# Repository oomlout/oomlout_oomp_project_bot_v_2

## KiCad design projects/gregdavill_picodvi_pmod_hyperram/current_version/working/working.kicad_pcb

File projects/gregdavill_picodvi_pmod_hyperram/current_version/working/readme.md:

# picodvi
 
## summary 
* id: gregdavill_picodvi_pmod_hyperram
* user: gregdavill
* name: picodvi
* board: pmod_hyperram
* repo: https://github.com/gregdavill/picodvi
* src_file_repo_kicad_pcb: hardware/pmod_hyperram/pmod_hyperram.kicad_pcb
* src_file_repo_kicad_pcb_link: https://github.com/gregdavill/picodvi/tree/master/hardware/pmod_hyperram/pmod_hyperram.kicad_pcb
* src_file_repo_kicad_sch: hardware/board/picodvi.kicad_sch
* src_file_repo_kicad_sch_link: https://github.com/gregdavill/picodvi/tree/master/hardware/board/picodvi.kicad_sch

* src_file_repo_sch: hardware/pmod_hyperram/pmod_hyperram.sch
* src_file_repo_sch_link: https://github.com/gregdavill/picodvi/tree/master/hardware/pmod_hyperram/pmod_hyperram.sch
* full details link: https://github.com/oomlout/oomlout_oomp_project_bot_v_2/tree/main/projects/gregdavill_picodvi_pmod_hyperram/current_version/working

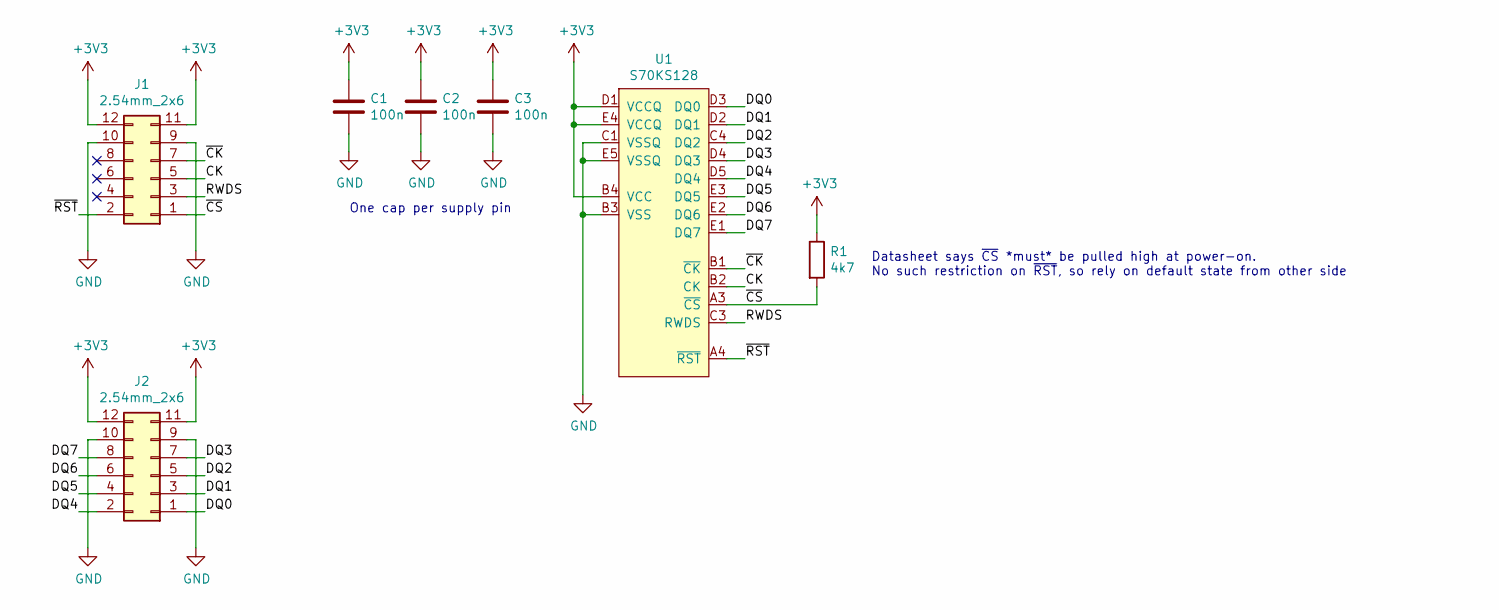
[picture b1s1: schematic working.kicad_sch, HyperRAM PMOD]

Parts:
C1, C2, C3: 100n; C_0402_1005Metric
J1, J2: 2.54mm_2x6; PinSocket_2x06_P2.54mm_Horizontal
R1: 4k7; R_0402_1005Metric
U1: S70KS128

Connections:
+3V3: C1.1, C2.1, C3.1, J1.11, J1.12, J2.11, J2.12, R1.1, U1.B4 (VCC), U1.D1 (VCCQ), U1.E4 (VCCQ)
/CK: J1.5, U1.B2 (CK)
/DQ0: J2.1, U1.D3 (DQ0)
/DQ1: J2.3, U1.D2 (DQ1)
/DQ2: J2.5, U1.C4 (DQ2)
/DQ3: J2.7, U1.D4 (DQ3)
/DQ4: J2.2, U1.D5 (DQ4)
/DQ5: J2.4, U1.E3 (DQ5)
/DQ6: J2.6, U1.E2 (DQ6)
/DQ7: J2.8, U1.E1 (DQ7)
/RWDS: J1.3, U1.C3 (RWDS)
/~CK: J1.7, U1.B1 (~CK)
/~CS: J1.1, R1.2, U1.A3 (~CS)
/~RST: J1.2, U1.A4 (~RST)
GND: C1.2, C2.2, C3.2, J1.9, J1.10, J2.9, J2.10, U1.B3 (VSS), U1.C1 (VSSQ), U1.E5 (VSSQ)

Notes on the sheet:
Datasheet says ~{CS} *must* be pulled high at power-on. No such restriction on ~{RST}, so rely on default state from other side
One cap per supply pin

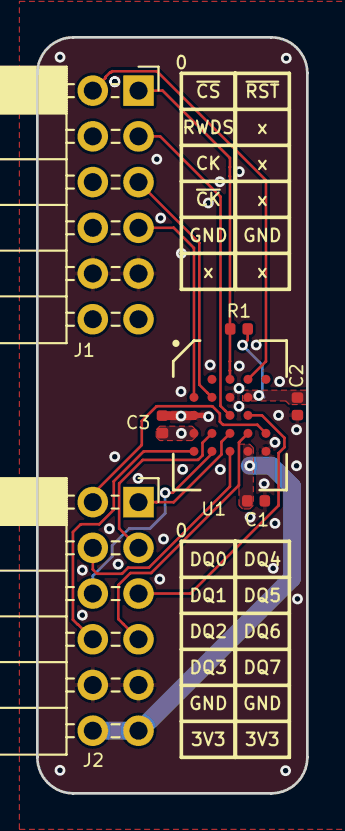
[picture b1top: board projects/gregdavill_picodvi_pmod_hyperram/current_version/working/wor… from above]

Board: 2 copper layers, 15.0 x 42.0 mm, 7 parts (0 on the bottom side), 15 nets.

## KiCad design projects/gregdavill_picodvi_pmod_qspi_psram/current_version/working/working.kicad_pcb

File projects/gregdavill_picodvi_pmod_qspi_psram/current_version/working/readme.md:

# picodvi
 
## summary 
* id: gregdavill_picodvi_pmod_qspi_psram
* user: gregdavill
* name: picodvi
* board: pmod_qspi_psram
* repo: https://github.com/gregdavill/picodvi
* src_file_repo_kicad_pcb: hardware/pmod_qspi_psram/pmod_qspi_psram.kicad_pcb
* src_file_repo_kicad_pcb_link: https://github.com/gregdavill/picodvi/tree/master/hardware/pmod_qspi_psram/pmod_qspi_psram.kicad_pcb
* src_file_repo_kicad_sch: hardware/board/picodvi.kicad_sch
* src_file_repo_kicad_sch_link: https://github.com/gregdavill/picodvi/tree/master/hardware/board/picodvi.kicad_sch

* src_file_repo_sch: hardware/pmod_qspi_psram/pmod_qspi_psram.sch
* src_file_repo_sch_link: https://github.com/gregdavill/picodvi/tree/master/hardware/pmod_qspi_psram/pmod_qspi_psram.sch
* full details link: https://github.com/oomlout/oomlout_oomp_project_bot_v_2/tree/main/projects/gregdavill_picodvi_pmod_qspi_psram/current_version/working

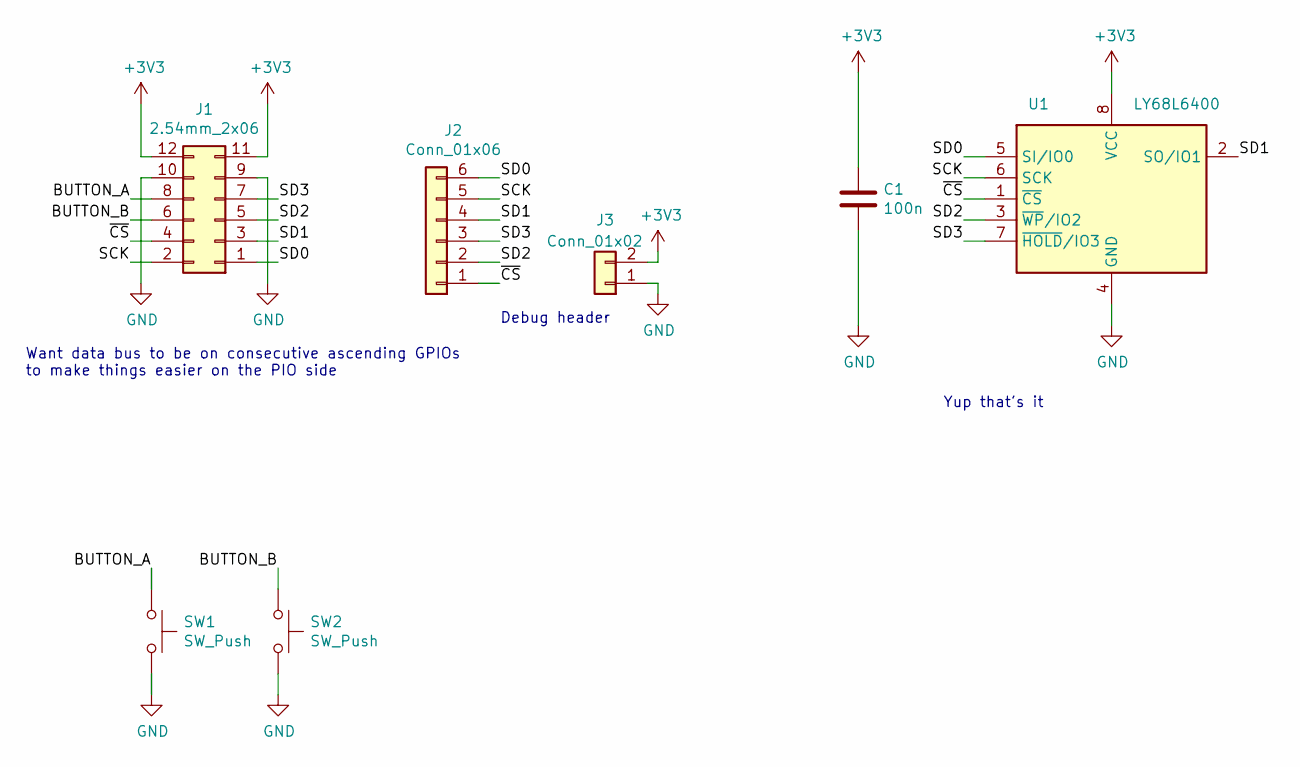
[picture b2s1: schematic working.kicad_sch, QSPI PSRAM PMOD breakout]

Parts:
C1: 100n; C_0402_1005Metric
J1: 2.54mm_2x06; PinSocket_2x06_P2.54mm_Horizontal
J2: Conn_01x06; PinHeader_1x06_P2.54mm_Vertical
J3: Conn_01x02; PinHeader_1x02_P2.54mm_Vertical
SW1, SW2: SW_Push; SW_SPST_PTS815
U1: LY68L6400; SOIC-8_3.9x4.9mm_P1.27mm

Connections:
+3V3: C1.1, J1.11, J1.12, J3.2, U1.8 (VCC)
/BUTTON_A: J1.8, SW1.1
/BUTTON_B: J1.6, SW2.1
/SCK: J1.2, J2.5, U1.6 (SCK)
/SD0: J1.1, J2.6, U1.5 (SI/IO0)
/SD1: J1.3, J2.4, U1.2 (SO/IO1)
/SD2: J1.5, J2.2, U1.3 (~WP/IO2)
/SD3: J1.7, J2.3, U1.7 (~HOLD/IO3)
/~CS: J1.4, J2.1, U1.1 (~CS)
GND: C1.2, J1.9, J1.10, J3.1, SW1.2, SW2.2, U1.4 (GND)

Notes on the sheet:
Yup that's it
Want data bus to be on consecutive ascending GPIOs to make things easier on the PIO side
Debug header

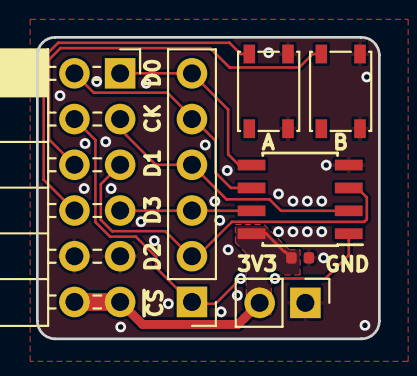
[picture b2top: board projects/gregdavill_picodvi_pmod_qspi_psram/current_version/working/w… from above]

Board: 2 copper layers, 19.0 x 16.8 mm, 7 parts (0 on the bottom side), 10 nets.

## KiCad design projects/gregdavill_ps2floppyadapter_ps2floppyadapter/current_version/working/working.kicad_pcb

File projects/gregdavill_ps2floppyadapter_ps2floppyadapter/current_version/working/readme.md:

# ps2floppyadapter
 
## summary 
* id: gregdavill_ps2floppyadapter_ps2floppyadapter
* user: gregdavill
* name: ps2floppyadapter
* board: ps2floppyadapter
* repo: https://github.com/gregdavill/PS2FloppyAdapter
* src_file_repo_kicad_pcb: PS2FloppyAdapter.kicad_pcb
* src_file_repo_kicad_pcb_link: https://github.com/gregdavill/PS2FloppyAdapter/tree/master/PS2FloppyAdapter.kicad_pcb

* src_file_repo_sch: PS2FloppyAdapter.sch
* src_file_repo_sch_link: https://github.com/gregdavill/PS2FloppyAdapter/tree/master/PS2FloppyAdapter.sch
* full details link: https://github.com/oomlout/oomlout_oomp_project_bot_v_2/tree/main/projects/gregdavill_ps2floppyadapter_ps2floppyadapter/current_version/working

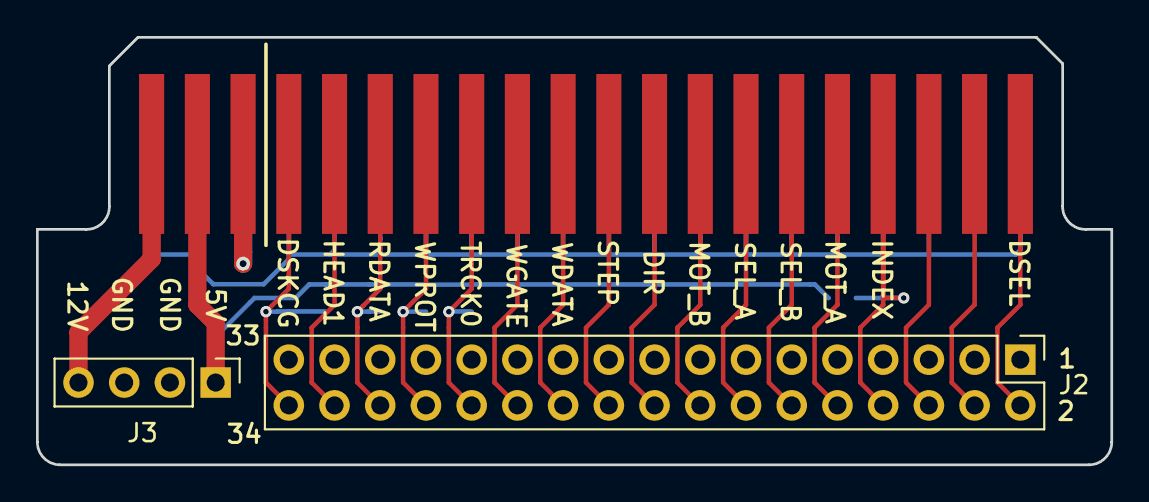
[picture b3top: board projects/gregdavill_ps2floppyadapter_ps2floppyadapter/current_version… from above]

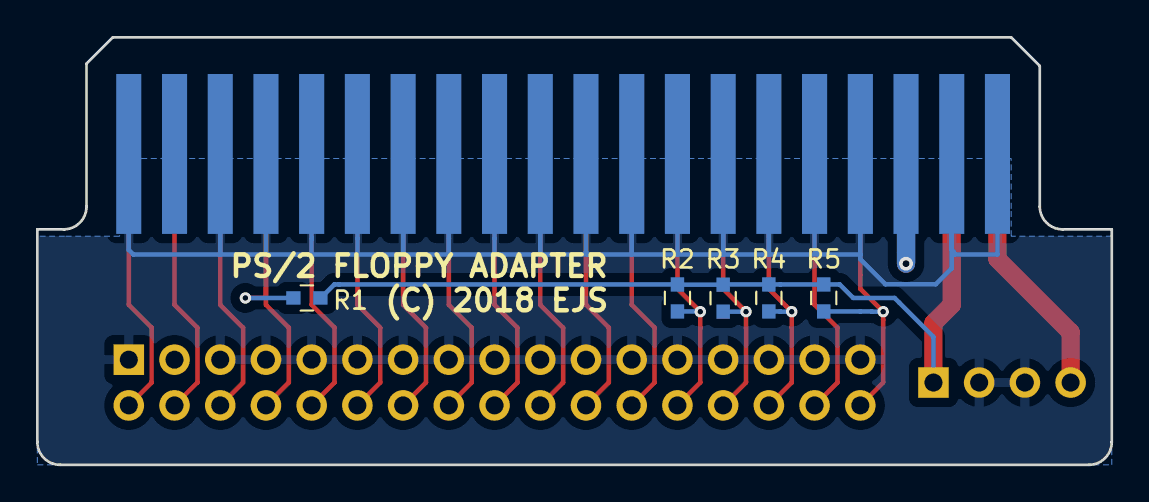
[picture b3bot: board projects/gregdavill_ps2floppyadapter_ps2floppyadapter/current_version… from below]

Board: 2 copper layers, 59.7 x 23.7 mm, 8 parts (5 on the bottom side), 21 nets.

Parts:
J1: Conn_02x20_Odd_Even; EDGE_FLOPPY40
J2: Conn_02x17_Odd_Even; Pin_Header_Straight_2x17_Pitch2.54mm
J3: Conn_01x04; Pin_Header_Straight_1x04_Pitch2.54mm
R1, R2, R3, R4, R5: 1K; RESC1608X55

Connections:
+5V: J1.38, J3.1, R1.1, R2.1, R3.1, R4.1, R5.1
+12V: J1.40, J3.4
/DIR: J1.18, J2.18
/DISKCHG: J1.34, J2.34, R5.2
/DSEL_A: J1.14, J2.14
/DSEL_B: J1.12, J2.12
/ENWRITE: J1.24, J2.24
/HDSEL: J1.2, J2.2
/HEAD1SEL: J1.32, J2.32
/INDEX: J1.8, J2.8, R1.2
/MOTEN_A: J1.10, J2.10
/MOTEN_B: J1.16, J2.16
/RDATA: J1.30, J2.30, R4.2
/RES1: J1.4, J2.4
/RES2: J1.6, J2.6
/STEP: J1.20, J2.20
/TRACK0: J1.26, J2.26, R2.2
/WDATA: J1.22, J2.22
/WPROT: J1.28, J2.28, R3.2
GND: J1.1, J1.5, J1.7, J1.9, J1.11, J1.13, J1.15, J1.17, J1.19, J1.21, J1.23, J1.25, J1.27, J1.29, J1.31, J1.33, J1.37, J1.39, J2.1, J2.5, J2.7, J2.9, J2.11, J2.13, J2.15, J2.17, J2.19, J2.21, J2.23, J2.25, J2.27, J2.29, J2.31, J2.33, J3.2, J3.3
unnamed: J1.35, J1.36

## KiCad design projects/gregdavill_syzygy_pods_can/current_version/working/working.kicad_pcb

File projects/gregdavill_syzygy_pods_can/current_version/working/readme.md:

# syzygy_pods
 
## summary 
* id: gregdavill_syzygy_pods_can
* user: gregdavill
* name: syzygy_pods
* board: can
* repo: https://github.com/gregdavill/syzygy-pods
* src_file_repo_kicad_pcb: hardware/can/can.kicad_pcb
* src_file_repo_kicad_pcb_link: https://github.com/gregdavill/syzygy-pods/tree/master/hardware/can/can.kicad_pcb
* src_file_repo_kicad_sch: hardware/can/can.kicad_sch
* src_file_repo_kicad_sch_link: https://github.com/gregdavill/syzygy-pods/tree/master/hardware/can/can.kicad_sch

* src_file_repo_sch: 
* src_file_repo_sch_link: https://github.com/gregdavill/syzygy-pods/tree/master/
* full details link: https://github.com/oomlout/oomlout_oomp_project_bot_v_2/tree/main/projects/gregdavill_syzygy_pods_can/current_version/working

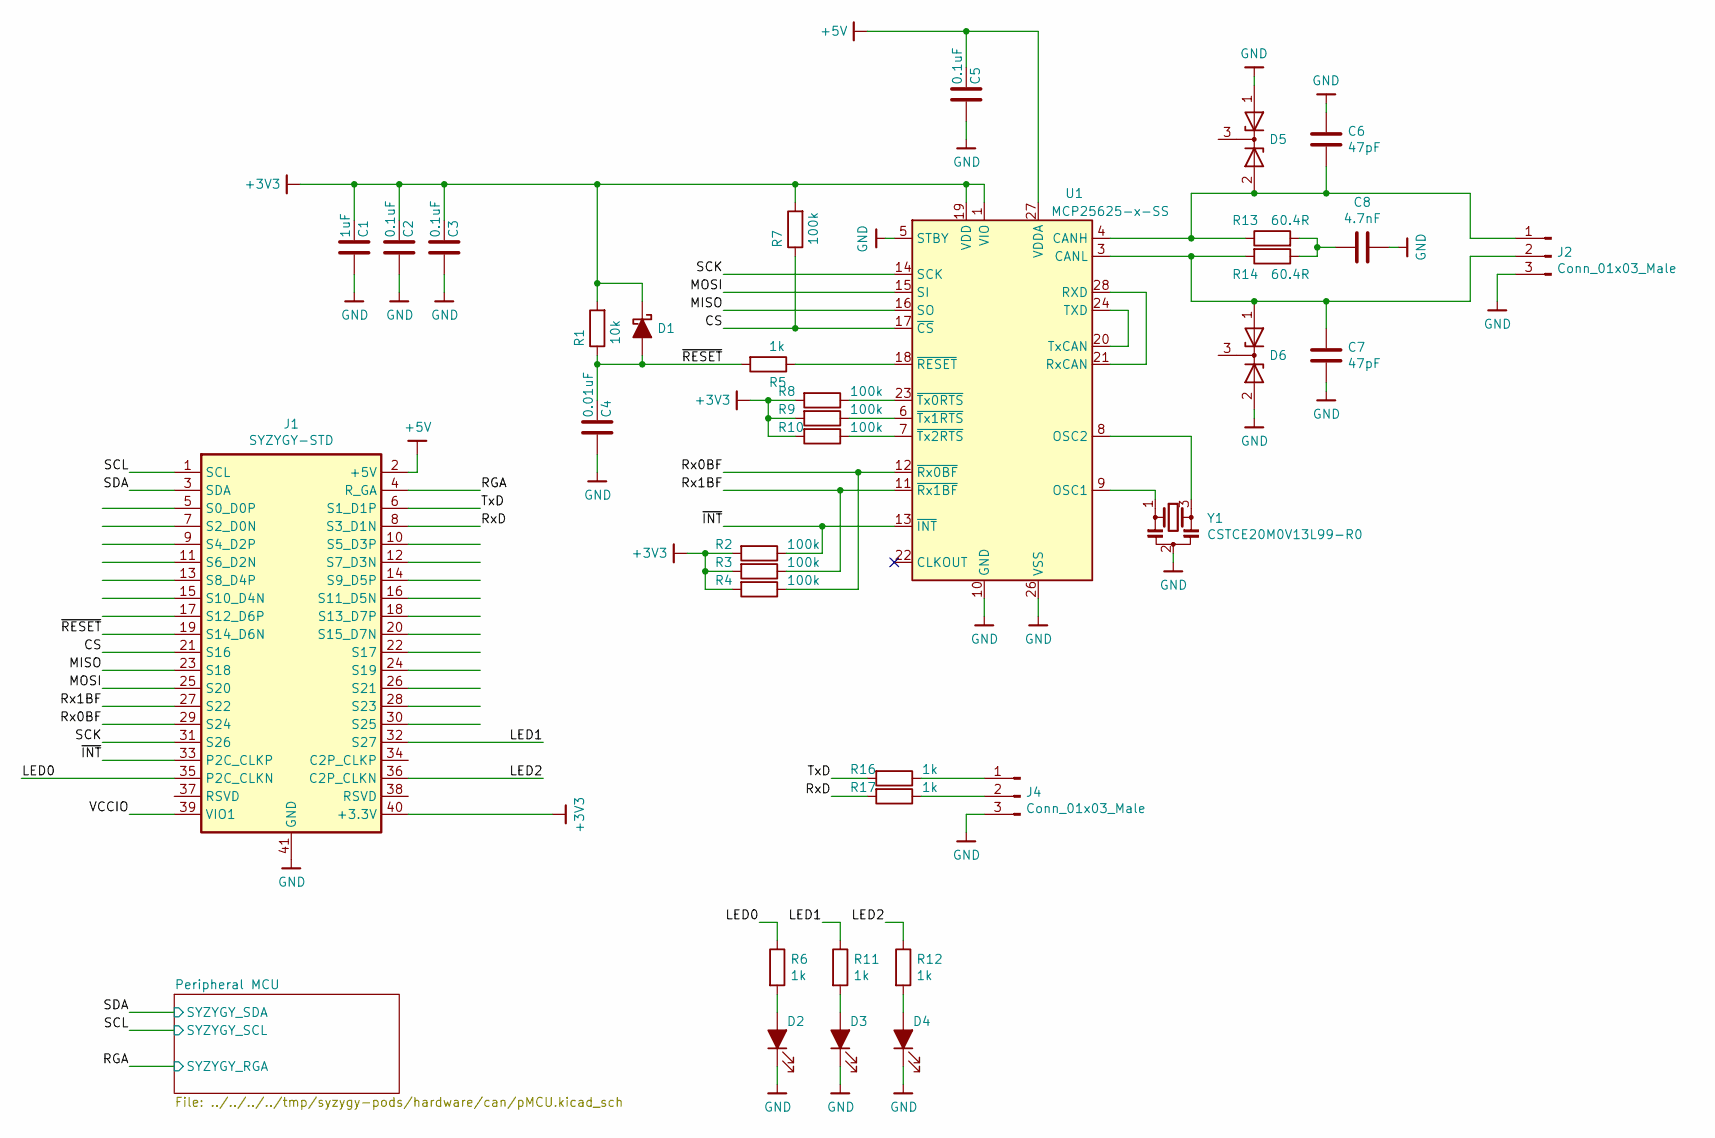
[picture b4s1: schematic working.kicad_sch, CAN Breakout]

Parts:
C1: 1uF; C_0402_1005Metric
C2, C3, C5: 0.1uF; C_0402_1005Metric
C4: 0.01uF; C_0402_1005Metric
C6, C7: 47pF; C_0805_2012Metric
C8: 4.7nF; C_0402_1005Metric
D1: D_Schottky_ALT; D_SOD-523
D2, D3, D4: LED_ALT; LED_0402_1005Metric
D5, D6: D_Zener_x2_KCom_AAK; SOT-23
J1: SYZYGY-STD; SYZYGY_standard_pod
J2: Conn_01x03_Male; PhoenixContact_MCV_1,5_3-G-3.5_1x03_P3.50mm_Vertical
J4: Conn_01x03_Male; PinHeader_1x03_P2.54mm_Vertical
R1: 10k; R_0402_1005Metric
R2, R3, R4, R7, R8, R9, R10: 100k; R_0402_1005Metric
R5, R6, R11, R12, R16, R17: 1k; R_0402_1005Metric
R13, R14: 60.4R; R_0805_2012Metric
U1: MCP25625-x-SS; SSOP-28_5.3x10.2mm_P0.65mm
Y1: CSTCE20M0V13L99-R0; Resonator_SMD_muRata_CSTxExxV-3Pin_3.0x1.1mm

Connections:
+3V3: C1.1, C2.1, C3.1, D1.1 (K), J1.40 (+3.3V), R1.2, R2.2, R3.2, R4.2, R7.2, R8.2, R9.2, R10.2, U1.1 (VIO), U1.19 (VDD); also elsewhere on the board
+5V: C5.1, J1.2 (+5V), U1.27 (VDDA)
/CS: J1.21 (S16), R7.1, U1.17 (~CS)
/LED0: J1.35 (P2C_CLKN), R6.1
/LED1: J1.32 (S27), R11.1
/LED2: J1.36 (C2P_CLKN), R12.1
/MISO: J1.23 (S18), U1.16 (SO)
/MOSI: J1.25 (S20), U1.15 (SI)
/RGA: J1.4 (R_GA); also elsewhere on the board
/Rx0BF: J1.29 (S24), R4.1, U1.12 (~Rx0BF)
/Rx1BF: J1.27 (S22), R3.1, U1.11 (~Rx1BF)
/RxD: J1.8 (S3_D1N), R17.2
/SCK: J1.31 (S26), U1.14 (SCK)
/SCL: J1.1 (SCL); also elsewhere on the board
/SDA: J1.3 (SDA); also elsewhere on the board
/TxD: J1.6 (S1_D1P), R16.2
/~INT: J1.33 (P2C_CLKP), R2.1, U1.13 (~INT)
/~RESET: C4.1, D1.2 (A), J1.19 (S14_D6N), R1.1, R5.2
GND: C1.2, C2.2, C3.2, C4.2, C5.2, C6.2, C7.1, C8.2, D2.1 (K), D3.1 (K), D4.1 (K), D5.1 (A), D6.2 (A), J1.41 (GND), J2.3, J4.3, U1.5 (STBY), U1.10 (GND), U1.26 (VSS), Y1.2; also elsewhere on the board
unnamed: C6.1, D5.2 (A), J2.1, R13.1, U1.4 (CANH)
unnamed: C7.2, D6.1 (A), J2.2, R14.2, U1.3 (CANL)
unnamed: C8.1, R13.2, R14.1
unnamed: D2.2 (A), R6.2
unnamed: D3.2 (A), R11.2
unnamed: D4.2 (A), R12.2
unnamed: J4.1, R16.1
unnamed: J4.2, R17.1
unnamed: R5.1, U1.18 (~RESET)
unnamed: R8.1, U1.23 (~Tx0RTS)
unnamed: R9.1, U1.6 (~Tx1RTS)
unnamed: R10.1, U1.7 (~Tx2RTS)
unnamed: U1.8 (OSC2), Y1.3
unnamed: U1.9 (OSC1), Y1.1
unnamed: U1.20 (TxCAN), U1.24 (TXD)
unnamed: U1.21 (RxCAN), U1.28 (RXD)

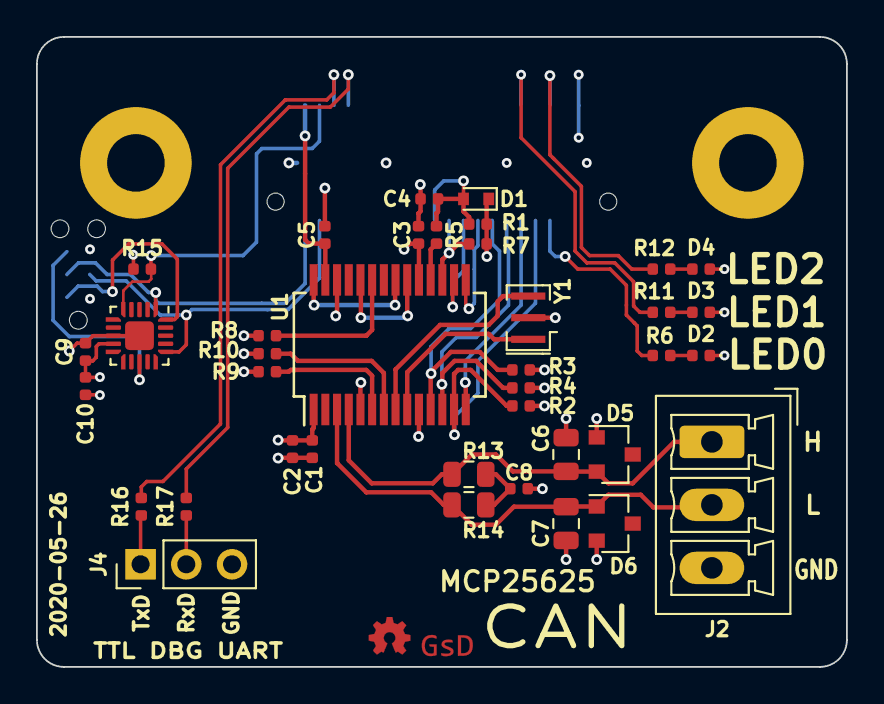
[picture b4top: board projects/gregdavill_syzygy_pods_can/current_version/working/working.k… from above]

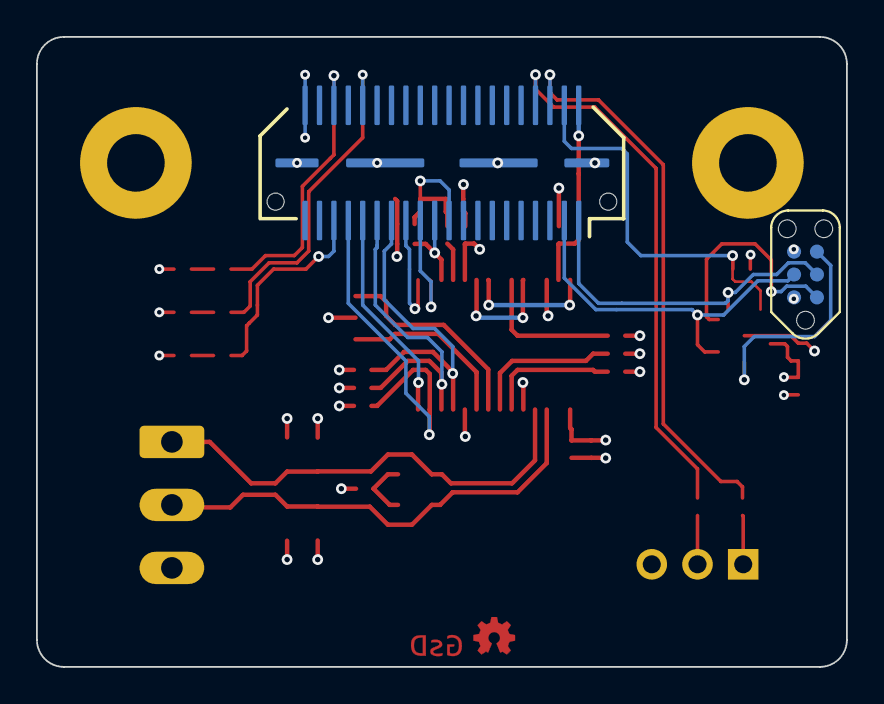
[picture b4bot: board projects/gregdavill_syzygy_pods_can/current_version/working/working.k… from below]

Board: 4 copper layers, 45.0 x 35.0 mm, 40 parts (2 on the bottom side), 37 nets.

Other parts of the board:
C9: 0.1uF; C_0402_1005Metric
C10: 1uF; C_0402_1005Metric
J3: TagConnect; TC2030-NL_SMALL
R15: 10K; R_0402_1005Metric
U2: ATtiny44A-MMH; QFN-20-1EP_3x3mm_P0.45mm_EP1.6x1.6mm

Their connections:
+3V3: C9.1, C10.1, J3.2, R15.1, U2.9 (VCC); also elsewhere on the board
/Peripheral MCU/MISO: J3.1, U2.20 (PA5)
/Peripheral MCU/~RESET: J3.5, U2.13 (~RESET~/PB3)
/RGA: R15.2, U2.5 (AREF/PA0); also elsewhere on the board
/SCL: J3.3, U2.1 (PA4); also elsewhere on the board
/SDA: J3.4, U2.16 (PA6); also elsewhere on the board
GND: C9.2, C10.2, J3.6, U2.8 (GND), U2.21 (GND); also elsewhere on the board

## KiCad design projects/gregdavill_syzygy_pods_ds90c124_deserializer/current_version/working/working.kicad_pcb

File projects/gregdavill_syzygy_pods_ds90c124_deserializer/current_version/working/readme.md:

# syzygy_pods
 
## summary 
* id: gregdavill_syzygy_pods_ds90c124_deserializer
* user: gregdavill
* name: syzygy_pods
* board: ds90c124_deserializer
* repo: https://github.com/gregdavill/syzygy-pods
* src_file_repo_kicad_pcb: hardware/ds90c124-deserializer/ds90c124-deserializer.kicad_pcb
* src_file_repo_kicad_pcb_link: https://github.com/gregdavill/syzygy-pods/tree/master/hardware/ds90c124-deserializer/ds90c124-deserializer.kicad_pcb
* src_file_repo_kicad_sch: hardware/ds90c124-deserializer/ds90c124-deserializer.kicad_sch
* src_file_repo_kicad_sch_link: https://github.com/gregdavill/syzygy-pods/tree/master/hardware/ds90c124-deserializer/ds90c124-deserializer.kicad_sch

* src_file_repo_sch: 
* src_file_repo_sch_link: https://github.com/gregdavill/syzygy-pods/tree/master/
* full details link: https://github.com/oomlout/oomlout_oomp_project_bot_v_2/tree/main/projects/gregdavill_syzygy_pods_ds90c124_deserializer/current_version/working

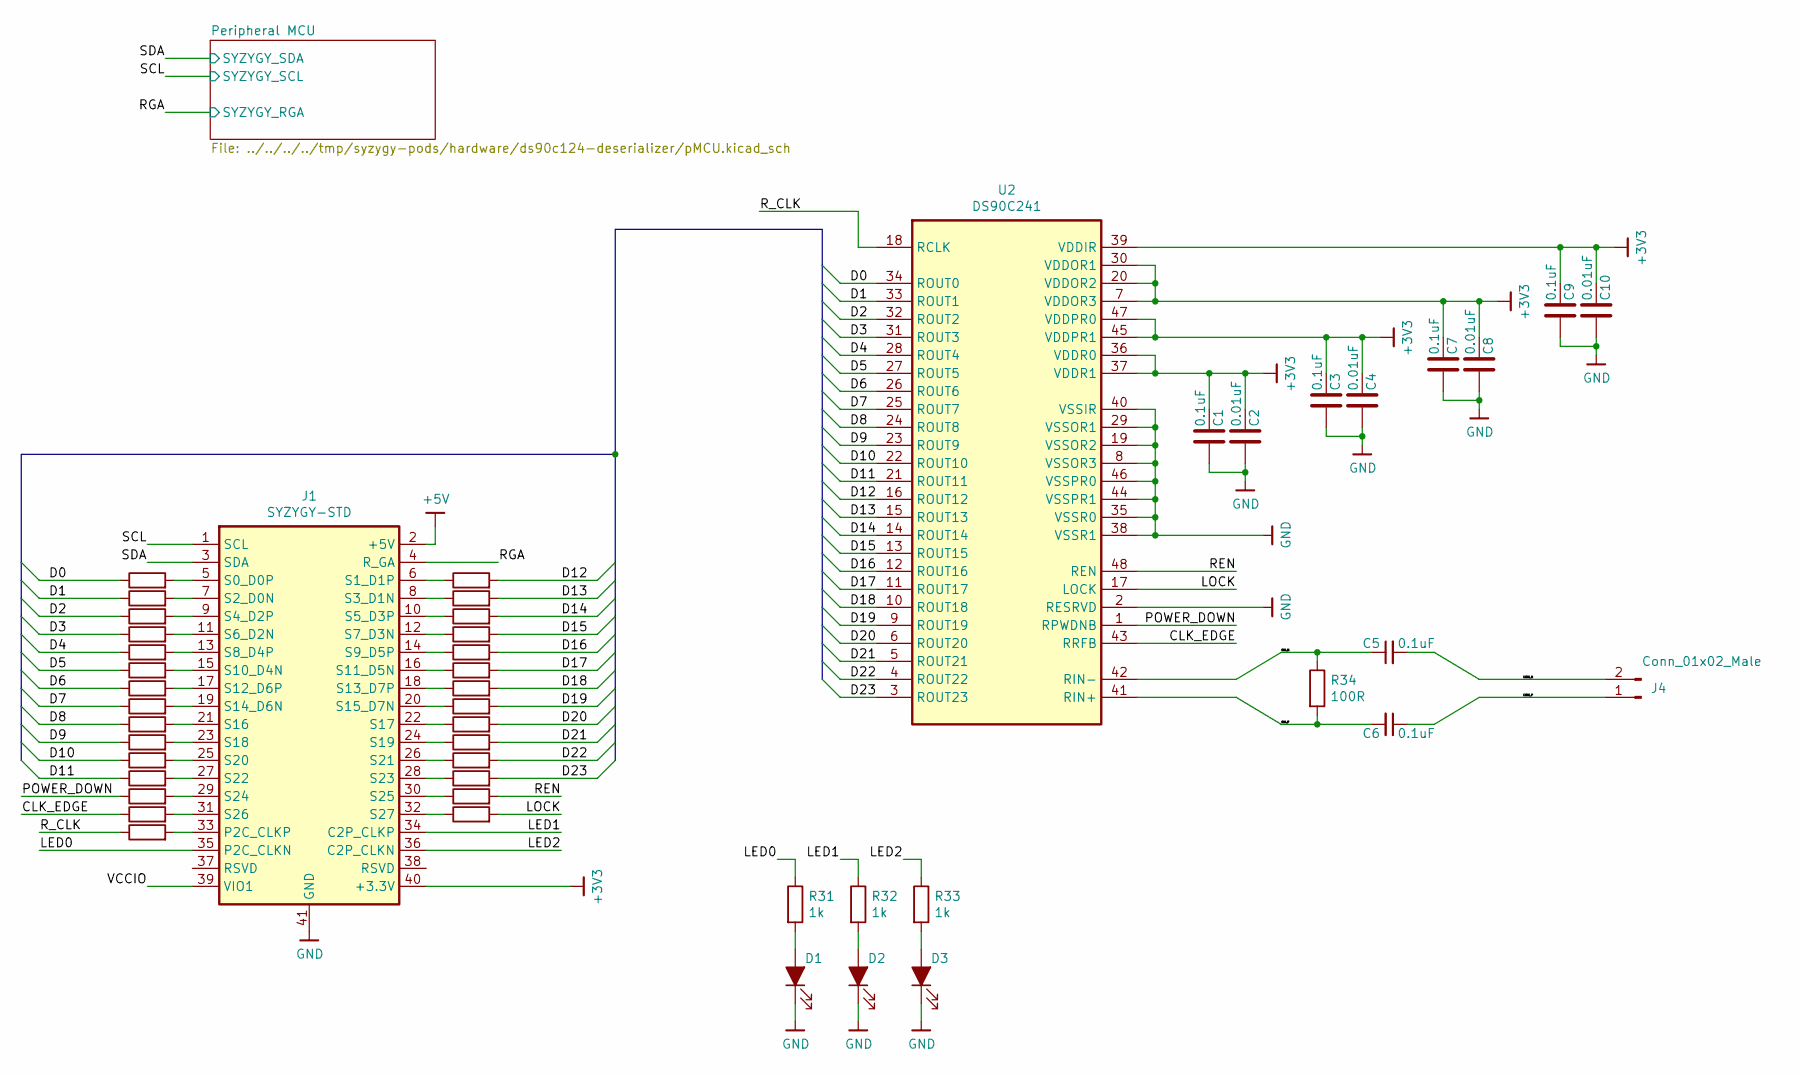
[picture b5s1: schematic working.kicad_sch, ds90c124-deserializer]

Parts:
C1, C3, C5, C6, C7, C9: 0.1uF; C_0402_1005Metric
C2, C4, C8, C10: 0.01uF; C_0402_1005Metric
D1, D2, D3: LED_ALT; LED_0402_1005Metric
J1: SYZYGY-STD; SYZYGY_standard_pod
J4: Conn_01x02_Male; SB02B-PASK-2
R2, R3, R4, R5, R6, R7, R8, R9, R10, R11, R12, R13, R14, R15, R16, R17, R18, R19, R20, R21, R22, R23, R24, R25, R26, R27, R28, R29, R30: 47R; R_0402_1005Metric
R31, R32, R33: 1k; R_0402_1005Metric
R34: 100R; R_0402_1005Metric
U2: DS90C241; LQFP-48_7x7mm_P0.5mm

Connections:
+3V3: C1.1, C2.1, C3.1, C4.1, C7.1, C8.1, C9.1, C10.1, J1.40 (+3.3V), U2.7 (VDDOR3), U2.20 (VDDOR2), U2.30 (VDDOR1), U2.36 (VDDR0), U2.37 (VDDR1), U2.39 (VDDIR), U2.45 (VDDPR1), U2.47 (VDDPR0); also elsewhere on the board
/CLK_EDGE: R15.1, U2.43 (RRFB)
/D0: R2.1, U2.34 (ROUT0)
/D1: R3.1, U2.33 (ROUT1)
/D2: R4.1, U2.32 (ROUT2)
/D3: R5.1, U2.31 (ROUT3)
/D4: R6.1, U2.28 (ROUT4)
/D5: R7.1, U2.27 (ROUT5)
/D6: R8.1, U2.26 (ROUT6)
/D7: R9.1, U2.25 (ROUT7)
/D8: R10.1, U2.24 (ROUT8)
/D9: R11.1, U2.23 (ROUT9)
/D10: R12.1, U2.22 (ROUT10)
/D11: R13.1, U2.21 (ROUT11)
/D12: R17.2, U2.16 (ROUT12)
/D13: R18.2, U2.15 (ROUT13)
/D14: R19.2, U2.14 (ROUT14)
/D15: R20.2, U2.13 (ROUT15)
/D16: R21.2, U2.12 (ROUT16)
/D17: R22.2, U2.11 (ROUT17)
/D18: R23.2, U2.10 (ROUT18)
/D19: R24.2, U2.9 (ROUT19)
/D20: R25.2, U2.6 (ROUT20)
/D21: R26.2, U2.5 (ROUT21)
/D22: R27.2, U2.4 (ROUT22)
/D23: R28.2, U2.3 (ROUT23)
/LED0: J1.35 (P2C_CLKN), R31.1
/LED1: J1.34 (C2P_CLKP), R32.1
/LED2: J1.36 (C2P_CLKN), R33.1
/LOCK: R30.2, U2.17 (LOCK)
/LVDS_N: C5.2, J4.2
/LVDS_P: C6.1, J4.1
/POWER_DOWN: R14.1, U2.1 (RPWDNB)
/REN: R29.2, U2.48 (REN)
/RGA: J1.4 (R_GA); also elsewhere on the board
/RIN_N: C5.1, R34.1, U2.42 (RIN-)
/RIN_P: C6.2, R34.2, U2.41 (RIN+)
/R_CLK: R16.1, U2.18 (RCLK)
/SCL: J1.1 (SCL); also elsewhere on the board
/SDA: J1.3 (SDA); also elsewhere on the board
GND: C1.2, C2.2, C3.2, C4.2, C7.2, C8.2, C9.2, C10.2, D1.1 (K), D2.1 (K), D3.1 (K), J1.41 (GND), U2.2 (RESRVD), U2.8 (VSSOR3), U2.19 (VSSOR2), U2.29 (VSSOR1), U2.35 (VSSR0), U2.38 (VSSR1), U2.40 (VSSIR), U2.44 (VSSPR1), U2.46 (VSSPR0); also elsewhere on the board
unnamed: D1.2 (A), R31.2
unnamed: D2.2 (A), R32.2
unnamed: D3.2 (A), R33.2
unnamed: J1.5 (S0_D0P), R2.2
unnamed: J1.6 (S1_D1P), R17.1
unnamed: J1.7 (S2_D0N), R3.2
unnamed: J1.8 (S3_D1N), R18.1
unnamed: J1.9 (S4_D2P), R4.2
unnamed: J1.10 (S5_D3P), R19.1
unnamed: J1.11 (S6_D2N), R5.2
unnamed: J1.12 (S7_D3N), R20.1
unnamed: J1.13 (S8_D4P), R6.2
unnamed: J1.14 (S9_D5P), R21.1
unnamed: J1.15 (S10_D4N), R7.2
unnamed: J1.16 (S11_D5N), R22.1
unnamed: J1.17 (S12_D6P), R8.2
unnamed: J1.18 (S13_D7P), R23.1
unnamed: J1.19 (S14_D6N), R9.2
unnamed: J1.20 (S15_D7N), R24.1
unnamed: J1.21 (S16), R10.2
unnamed: J1.22 (S17), R25.1
unnamed: J1.23 (S18), R11.2
unnamed: J1.24 (S19), R26.1
unnamed: J1.25 (S20), R12.2
unnamed: J1.26 (S21), R27.1
unnamed: J1.27 (S22), R13.2
unnamed: J1.28 (S23), R28.1
unnamed: J1.29 (S24), R14.2
unnamed: J1.30 (S25), R29.1
unnamed: J1.31 (S26), R15.2
unnamed: J1.32 (S27), R30.1
unnamed: J1.33 (P2C_CLKP), R16.2

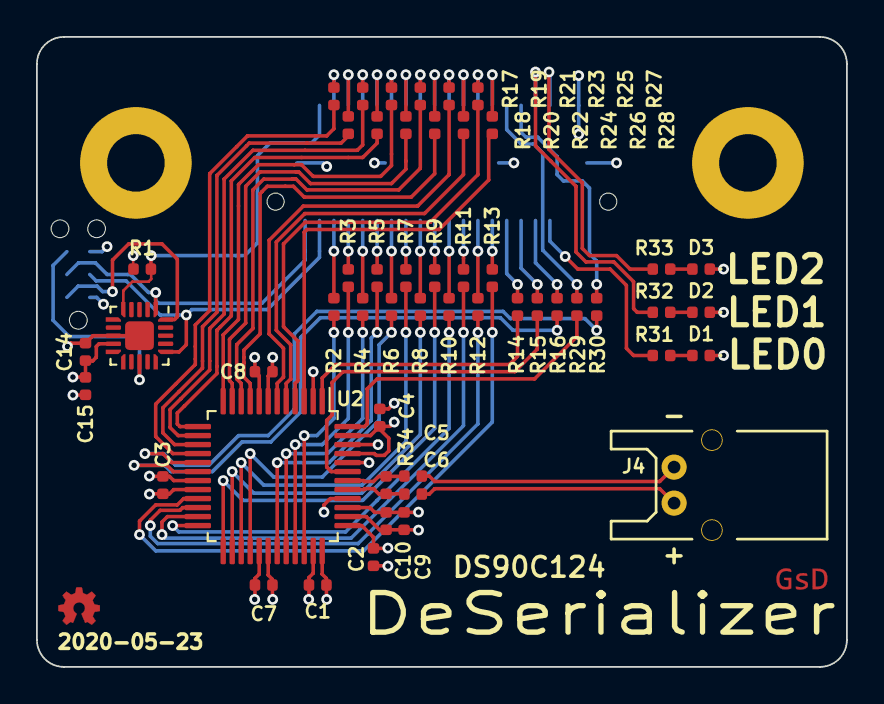
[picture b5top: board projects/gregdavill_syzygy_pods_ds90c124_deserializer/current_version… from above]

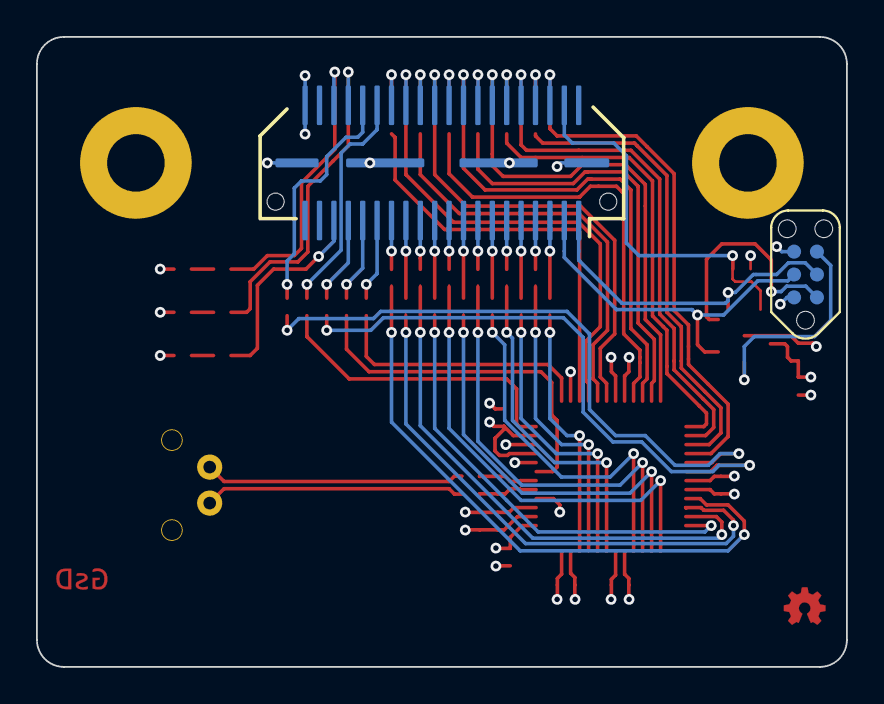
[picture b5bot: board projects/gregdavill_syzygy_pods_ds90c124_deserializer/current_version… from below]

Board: 4 copper layers, 45.0 x 35.0 mm, 54 parts (2 on the bottom side), 75 nets.

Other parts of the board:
C14: 0.1uF; C_0402_1005Metric
C15: 1uF; C_0402_1005Metric
J3: TagConnect; TC2030-NL_SMALL
R1: 10K; R_0402_1005Metric
U1: ATtiny44A-MMH; QFN-20-1EP_3x3mm_P0.45mm_EP1.6x1.6mm

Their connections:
+3V3: C14.1, C15.1, J3.2, R1.1, U1.9 (VCC); also elsewhere on the board
/Peripheral MCU/MISO: J3.1, U1.20 (PA5)
/Peripheral MCU/~RESET: J3.5, U1.13 (~RESET~/PB3)
/RGA: R1.2, U1.5 (AREF/PA0); also elsewhere on the board
/SCL: J3.3, U1.1 (PA4); also elsewhere on the board
/SDA: J3.4, U1.16 (PA6); also elsewhere on the board
GND: C14.2, C15.2, J3.6, U1.8 (GND), U1.21 (GND); also elsewhere on the board

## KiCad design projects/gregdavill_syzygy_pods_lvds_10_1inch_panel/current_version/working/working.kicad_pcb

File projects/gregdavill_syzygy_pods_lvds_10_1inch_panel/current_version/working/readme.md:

# syzygy_pods
 
## summary 
* id: gregdavill_syzygy_pods_lvds_10_1inch_panel
* user: gregdavill
* name: syzygy_pods
* board: lvds_10_1inch_panel
* repo: https://github.com/gregdavill/syzygy-pods
* src_file_repo_kicad_pcb: hardware/lvds-10.1inch-panel/lvds_10.1inch_panel.kicad_pcb
* src_file_repo_kicad_pcb_link: https://github.com/gregdavill/syzygy-pods/tree/master/hardware/lvds-10.1inch-panel/lvds_10.1inch_panel.kicad_pcb
* src_file_repo_kicad_sch: hardware/ds90c124-deserializer/ds90c124-deserializer.kicad_sch
* src_file_repo_kicad_sch_link: https://github.com/gregdavill/syzygy-pods/tree/master/hardware/ds90c124-deserializer/ds90c124-deserializer.kicad_sch

* src_file_repo_sch: hardware/lvds-10.1inch-panel/lvds_10.1inch_panel.sch
* src_file_repo_sch_link: https://github.com/gregdavill/syzygy-pods/tree/master/hardware/lvds-10.1inch-panel/lvds_10.1inch_panel.sch
* full details link: https://github.com/oomlout/oomlout_oomp_project_bot_v_2/tree/main/projects/gregdavill_syzygy_pods_lvds_10_1inch_panel/current_version/working

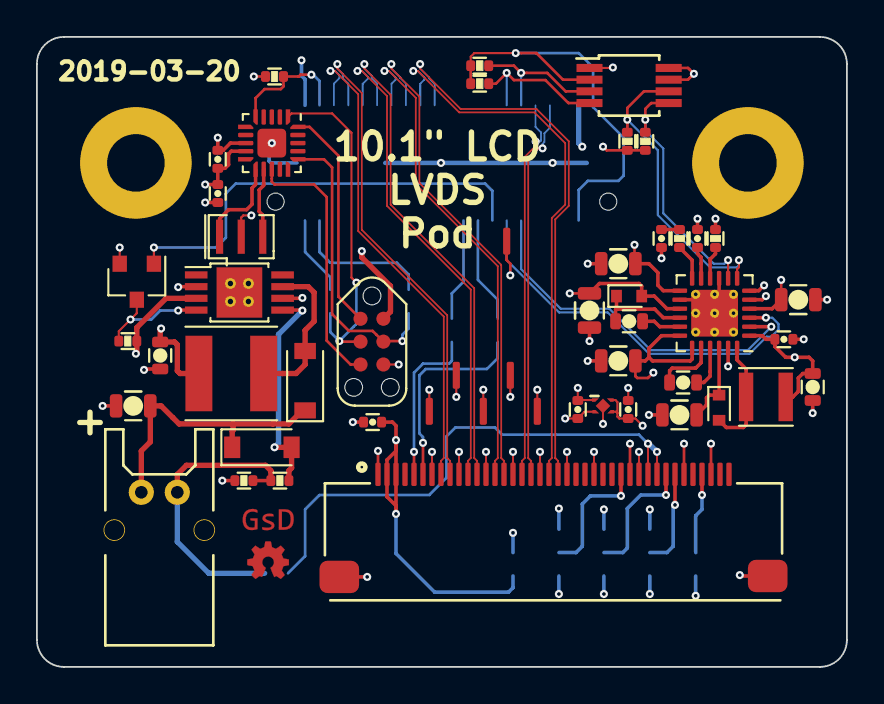
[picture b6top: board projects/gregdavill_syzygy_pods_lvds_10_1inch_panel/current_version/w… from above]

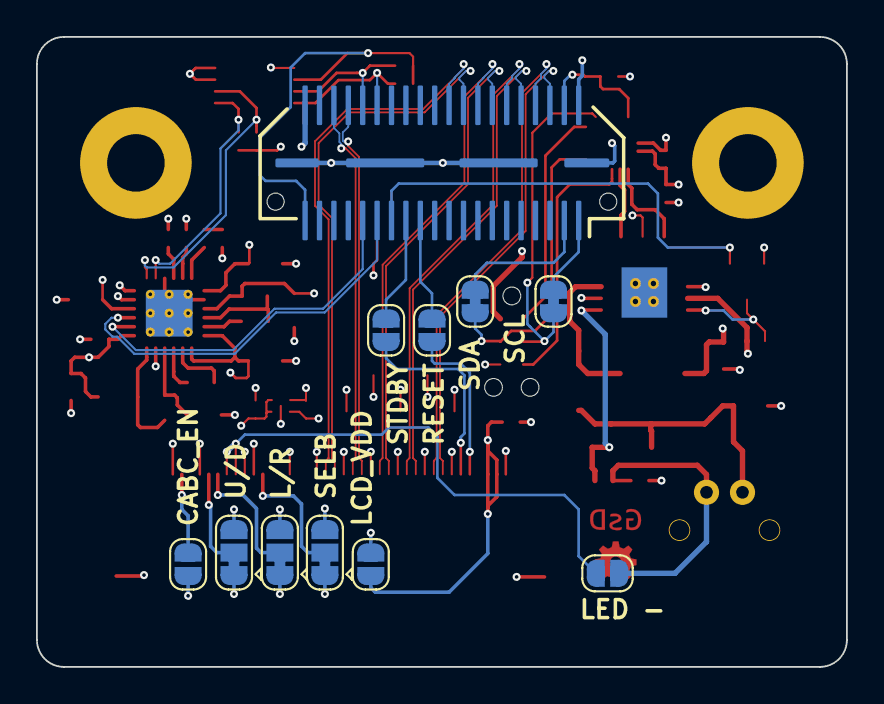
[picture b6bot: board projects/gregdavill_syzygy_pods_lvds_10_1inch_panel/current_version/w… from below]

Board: 4 copper layers, 45.0 x 35.0 mm, 55 parts (11 on the bottom side), 59 nets.

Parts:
C1, C3, C4, C14, C16: 100n; C_0402
C2, C12: 10uF; C_0603
C5, C6: 100n; C_0603
C7, C8, C9, C10, C11, C13: 10uF; C_0805
C15, C17: 1uF; C_0402
C18: 100nF; C_0402
D1, D2: D_Schottky_ALT; D_SOD-523
D3: D_Schottky_ALT; D_SOD-123
D4: 18V; D_SOD-123
J1: SYZYGY-STD; SYZYGY_standard_pod
J2: 40P 0.5MM FFC; FH28E-40S-0.5SH(05)
J3: TagConnect; TC2030-NL_SMALL
J4: JST PA2; SB02B-PASK-2
JP1, JP4, JP5, JP9: SolderJumper_2_Open; SolderJumper-2_P1.3mm_Open_RoundedPad1.0x1.5mm
JP2, JP3: SolderJumper_2_Bridged; SolderJumper-2_P1.3mm_Bridged_RoundedPad1.0x1.5mm
JP6, JP7, JP8: SolderJumper_3_Bridged12; SolderJumper-3_P1.3mm_Bridged12_RoundedPad1.0x1.5mm
JP10: SolderJumper_2_Bridged; SolderJumper-2_P1.3mm_Open_RoundedPad1.0x1.5mm
L1: L; L_Taiyo-Yuden_MD-3030
L2: L; L_Taiyo-Yuden_MD-5050
Q1: 2N7002; SOT-23
R1: 10K; R_0402
R2, R3, R4, R5, R6: 5K; R_0402
R9, R10, R11, R12: 2k2; R_0402
U1: ATtiny44A-MMH; QFN-20-1EP_3x3mm_P0.45mm_EP1.6x1.6mm
U2: A8603; QFN-24-1EP_4x4mm_P0.5mm_EP2.6x2.6mm_ThermalVias
U3: LM3410; MSOP-8-1EP_3x3mm_P0.65mm_EP2.54x2.8mm_ThermalVias
U4: PCA9306; MSOP-8_3x3mm_P0.65mm
U5: NCP167; X2SON_4_1.0x1.0mm
Y1: 8MHz; Resonator_SMD_muRata_CSTxExxV-3Pin_3.0x1.1mm

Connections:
+3V3: C14.1, C15.1, J1.40, J3.2, JP6.3, JP7.3, JP8.3, JP9.1, JP10.1, R1.1, U1.9
+5V: C1.1, C2.1, C12.1, C16.1, J1.2, L1.1, L2.1, R4.1, R11.1, R12.1, U2.1, U3.3, U4.7, U4.8, U5.3, U5.4
/AVDD: C8.1, J2.29, U2.13
/CABC_EN: J2.37, JP9.2
/CLK_N: J1.34, J2.17
/CLK_P: J1.36, J2.18
/LCD PMIC/LED+: C13.1, D3.1, D4.1, J4.1
/LCD PMIC/LED-: J4.2, JP1.1, R5.1, R6.2
/LCD PMIC/VOUT: C7.1, D1.1, U2.22
/LCD_DIM: J1.27, Q1.1
/LCD_EN: J1.29, U2.3
/LCD_PMIC_FAULT: J1.31, U2.2
/LCD_PMIC_SCL: J1.32, R9.2, U4.3
/LCD_PMIC_SDA: J1.30, R10.2, U4.4
/LED-: J2.31, J2.32, JP1.2
/L\R: J2.33, JP7.2
/Peripheral MCU/MISO: J3.1, U1.20
/Peripheral MCU/MOSI: J3.4, JP3.2, U1.16
/Peripheral MCU/SCK: J3.3, JP2.2, U1.1
/Peripheral MCU/~RESET: J3.5, U1.13
/RESET: J2.5, JP4.1
/RGA: J1.4, R1.2, U1.5
/RXIN_0_N: J1.6, J2.8
/RXIN_0_P: J1.8, J2.9
/RXIN_1_N: J1.10, J2.11
/RXIN_1_P: J1.12, J2.12
/RXIN_2_N: J1.14, J2.14
/RXIN_2_P: J1.16, J2.15
/RXIN_3_N: J1.18, J2.20
/RXIN_3_P: J1.20, J2.21
/SCL: J1.1, JP2.1
/SDA: J1.3, JP3.1
/SELB: J2.28, JP6.2
/STBYB: J2.6, JP5.1
/U\D: J2.34, JP8.2
/VCCIO: J1.39, R9.1, R10.1, U4.2
/VCOM: C9.1, J2.1, U2.4
/VDD: C17.1, C18.1, J2.2, J2.3, JP10.2, U5.1
/VGH: C10.1, J2.38, U2.18, U2.19
/VGL: C11.1, D2.2, J2.35, U2.15
GND: C1.2, C2.2, C3.2, C4.2, C7.2, C8.2, C9.2, C10.2, C11.2, C12.2, C13.2, C14.2, C15.2, C16.2, C17.2, C18.2, J1.41, J2.7, J2.10, J2.13, J2.16, J2.19, J2.22, J2.25, J2.30, J2.MP, J3.6, JP6.1, JP7.1, JP8.1, Q1.2, R2.2, R6.1, U1.8, U1.21, U2.5, U2.6, U2.9, U2.14, U2.23, U2.25, U3.2, U3.6, U3.9, U4.1, U5.2, Y1.2
unnamed: C3.1, U2.11
unnamed: C4.1, R3.1
unnamed: C5.1, U2.20
unnamed: C5.2, U2.21
unnamed: C6.1, U2.17
unnamed: C6.2, D2.1, U2.16
unnamed: D1.2, L1.2, U2.24
unnamed: D3.2, L2.2, U3.7
unnamed: D4.2, R5.2, U3.5
unnamed: J1.23, JP4.2
unnamed: J1.25, JP5.2
unnamed: Q1.3, R4.2, U3.4
unnamed: R2.1, U2.10
unnamed: R3.2, U2.12
unnamed: R11.2, U2.7, U4.6
unnamed: R12.2, U2.8, U4.5
unnamed: U1.11, Y1.1
unnamed: U1.12, Y1.3

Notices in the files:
projects/gregdavill_ps2floppyadapter_ps2floppyadapter/current_version/working/working.kicad_pcb:
Copyright (C) 2020 Eric Schlaepfer
License. See https://creativecommons.org/licenses/by-sa/4.0
This work is licensed under a Creative Commons Attribution-ShareAlike 4.0 International
(C) 2018 EJS
projects/gregdavill_ps2floppyadapter_ps2floppyadapter/current_version/working/working.kicad_sch:
This work is licensed under the Creative Commons
Attribution-ShareAlike 4.0 International License.
http://creativecommons.org/licenses/by-sa/4.0
or send a letter to Creative Commons, PO Box 1866,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
